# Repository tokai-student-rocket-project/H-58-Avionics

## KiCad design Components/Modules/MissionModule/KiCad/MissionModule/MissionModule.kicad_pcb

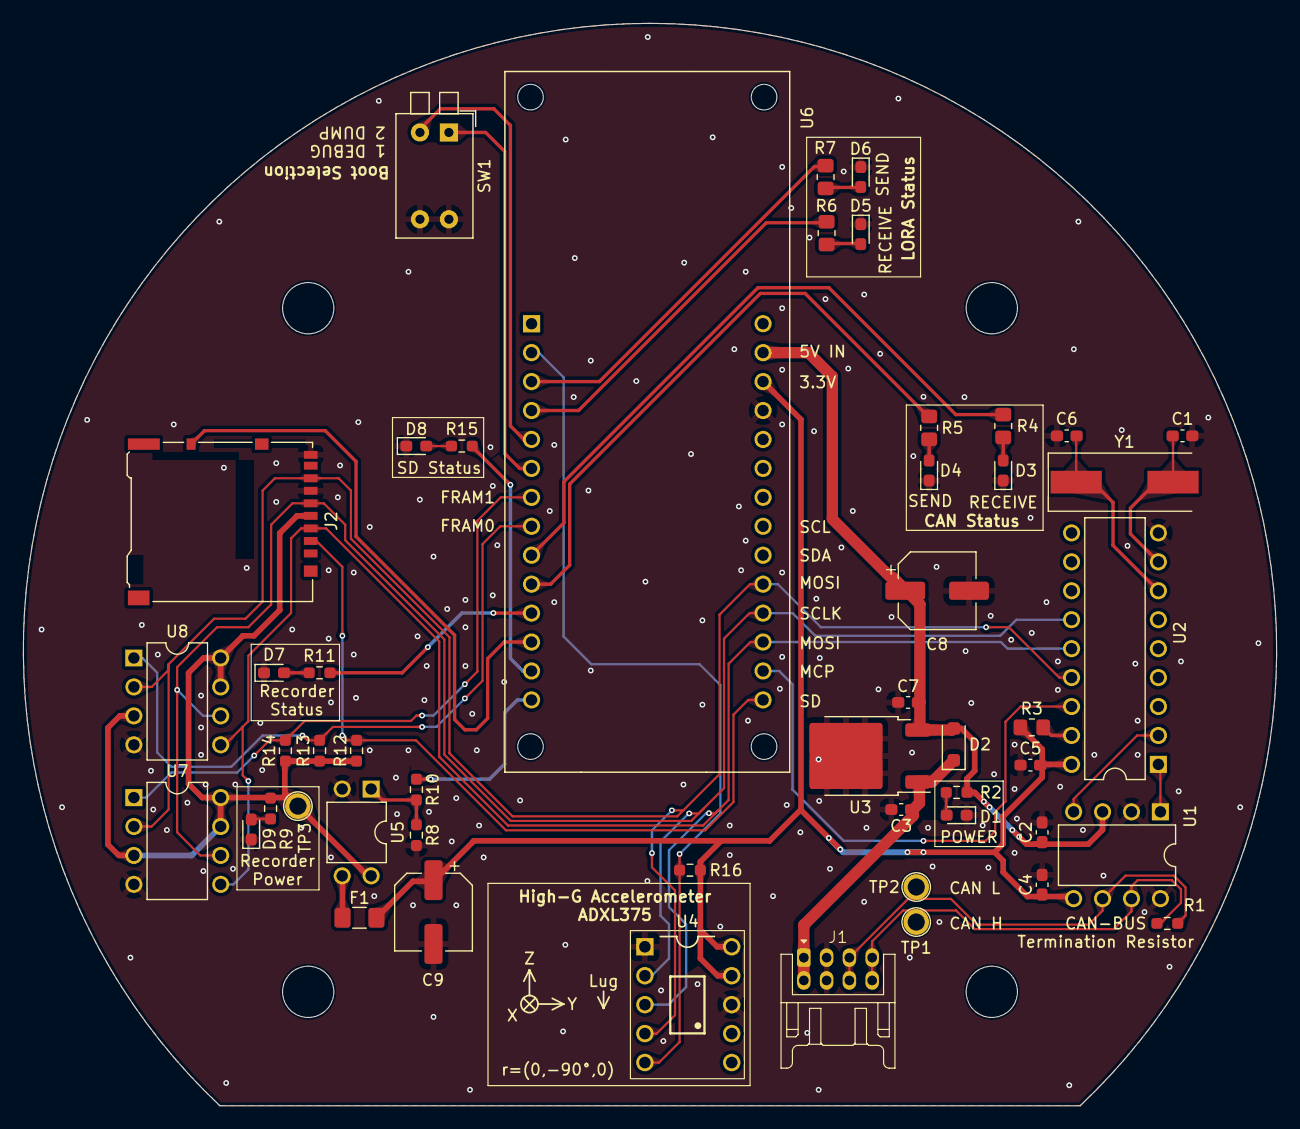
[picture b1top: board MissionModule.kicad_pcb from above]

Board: 2 copper layers, 110.0 x 95.0 mm, 50 parts (0 on the bottom side), 40 nets.

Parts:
C1, C6: 15pF; C_0603_1608Metric_Pad1.08x0.95mm_HandSolder
C2, C4, C5, C7: 0.1uF; C_0603_1608Metric_Pad1.08x0.95mm_HandSolder
C3: 10uF; C_0603_1608Metric_Pad1.08x0.95mm_HandSolder
C8, C9: 47uF; CP_Elec_6.3x5.9
D1, D9: RED; LED_0603_1608Metric_Pad1.05x0.95mm_HandSolder
D2: 1N4007; D_SOD-123F
D3, D4, D5, D6: BLUE; LED_0603_1608Metric_Pad1.05x0.95mm_HandSolder
D7, D8: GREEN; LED_0603_1608Metric_Pad1.05x0.95mm_HandSolder
F1: Polyfuse; Fuse_1206_3216Metric_Pad1.42x1.75mm_HandSolder
J1: Conn_01x08; Hirose_DF11B-8DP-2DS
J2: Micro_SD_Card_Det_Hirose_DM3AT; microSD_HC_Hirose_DM3AT-SF-PEJM5
R1, R8, R10: 120R; R_0603_1608Metric_Pad0.98x0.95mm_HandSolder
R2: 620R; R_0603_1608Metric_Pad0.98x0.95mm_HandSolder
R3: 10kR; R_0805_2012Metric_Pad1.20x1.40mm_HandSolder
R4, R5, R6, R7: 100R; R_0805_2012Metric_Pad1.20x1.40mm_HandSolder
R9, R11, R15: 300R; R_0603_1608Metric_Pad0.98x0.95mm_HandSolder
R12, R13, R14, R16: 4.7kR; R_0603_1608Metric_Pad0.98x0.95mm_HandSolder
SW1: SW_DIP_x02; SW_DIP_SPSTx02_Piano_10.8x6.64mm_W7.62mm_P2.54mm
TP1, TP2, TP3: TestPoint; Pin_D1.0mm_L10.0mm
U1: MCP2562-E-P; DIP-8_W7.62mm
U2: MCP2515-I/P; DIP-18_W7.62mm
U3: NJM7805SDL1; TO-252-2
U4: ADXL375
U5: TLP241B; DIP-4_W7.62mm
U6: ABX00012; ARDUINO_ABX00012
U7, U8: MB85RS2MT; DIP-8_W7.62mm
Y1: 8MHz; Crystal_SMD_HC49-SD

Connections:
+3.3V: C4.1, C5.1, C9.1, F1.1, R3.1, R16.1, U1.5 (Vio), U2.18 (VDD), U4.9 (VS), U4.10 (VDDI/O), U6.26 (+3V3)
+5V: C2.1, C7.1, C8.1, D2.2 (A), R2.1, U1.3 (VDD), U3.3 (OUT), U6.27 (VIN)
+12V: C3.1, D2.1 (K), J1.1, J1.2, U3.1 (IN)
CAN_H: J1.7, J1.8, R1.1, TP1.1, U1.7 (CANH)
CAN_L: J1.5, J1.6, R1.2, TP2.1, U1.6 (CANL)
CAN_RECEIVE_STATUS: R4.1, U6.9 (PA22_TC4-W0/0)
CAN_RX: U1.4 (RXD), U2.2 (RXCAN)
CAN_SEND_STATUS: R5.1, U6.10 (PA23_TC4-W1/1)
CAN_TX: U1.1 (TXD), U2.1 (TXCAN)
DEBUG_MODE: SW1.1, U6.6 (PA05_AIN5/A4)
DUMP_MODE: SW1.2, U6.5 (PA04_AIN4/A3)
GND: C1.1, C2.2, C3.2, C4.2, C5.2, C6.1, C7.2, C8.2, C9.2, D1.1 (K), D3.1 (K), D4.1 (K), D5.1 (K), D6.1 (K), D7.1 (K), D8.1 (K), D9.1 (K), J1.3, J1.4, J2.6 (VSS), J2.9 (DET_B), R8.2, SW1.3, SW1.4, U1.2 (VSS), U1.8 (STBY), U2.9 (VSS), U3.2 (GND), U4.1 (GND), U4.8 (GND), U5.2, U6.25 (GND), U7.4 (GND), U8.4 (GND)
LORA_RECEIVE_STATUS: R6.1, U6.4 (PB03_AIN11/A2)
LORA_SEND_STATUS: R7.1, U6.3 (PB02_AIN10/A1)
MEMORY_POWER: J2.4 (VDD), R9.1, R12.1, R13.1, R14.1, TP3.1, U5.4, U7.3 (~WP), U7.7 (~HOLD), U7.8 (VDD), U8.3 (~WP), U8.7 (~HOLD), U8.8 (VDD)
MEMORY_POWER_CONTROL: R10.1, U6.14 (PB11_TCC0-W5/~5)
unnamed: D1.2 (A), R2.2
unnamed: D3.2 (A), R4.2
unnamed: D4.2 (A), R5.2
unnamed: D5.2 (A), R6.2
unnamed: D6.2 (A), R7.2
unnamed: D7.2 (A), R11.2
unnamed: D8.2 (A), R15.2
unnamed: D9.2 (A), R9.2
unnamed: F1.2, U5.3
unnamed: R8.1, R10.2, U5.1
unnamed: R3.2, U2.17 (~RESET)
OSC1: C1.2, U2.8 (OSC1), Y1.2
OSC2: C6.2, U2.7 (OSC2), Y1.1
RECORD_STATUS: R11.1, U6.11 (PA10_TCC0-W2/~2)
SD_CHECK: J2.10 (DET_A), U6.12 (PA11_TCC0-W3/~3)
SD_STATUS: R15.1, U6.13 (PB10_TCC0-W4/~4)
SPI_CS_ADXL: R16.2, U4.5 (~CS), U6.2 (PA02_AIN0/DAC0/A0)
SPI_CS_FRAM0: R13.2, U6.8 (PA07_AIN7/A6), U8.1 (~CS)
SPI_CS_FRAM1: R14.2, U6.7 (PA06_AIN6/A5), U7.1 (~CS)
SPI_CS_MCP: U2.16 (~CS), U6.16 (PA21_TCC0-W7)
SPI_CS_SD: J2.2 (DAT3/CD), R12.2, U6.15 (PA20_TCC0-W6)
SPI_MISO: J2.7 (DAT0), U2.15 (SO), U4.4 (SDO/ALT_ADDRESS), U6.19 (PA19_S1_MISO), U7.2 (SO), U8.2 (SO)
SPI_MOSI: J2.3 (CMD), U2.14 (SI), U4.3 (SDA/SDI/SDIO), U6.17 (PA16_S1_MOSI), U7.5 (SI), U8.5 (SI)
SPI_SCLK: J2.5 (CLK), U2.13 (SCK), U4.2 (SCK/SCLK), U6.18 (PA17_S1_SCK), U7.6 (SCK), U8.6 (SCK)

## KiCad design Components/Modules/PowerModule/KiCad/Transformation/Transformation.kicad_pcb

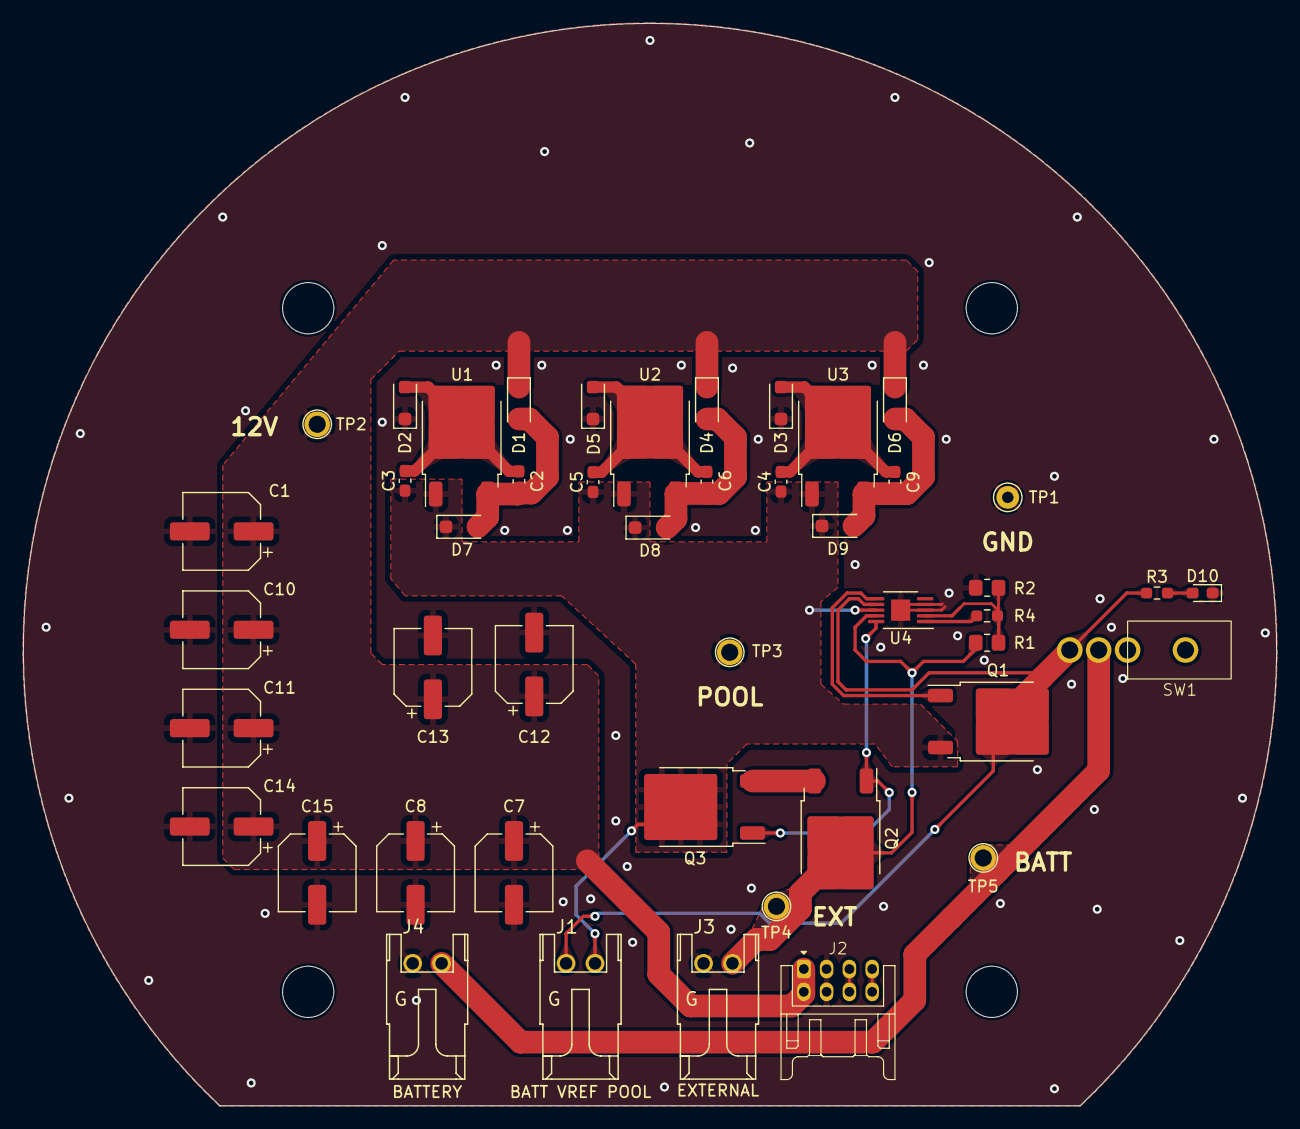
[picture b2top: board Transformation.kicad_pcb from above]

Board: 2 copper layers, 110.0 x 95.0 mm, 46 parts (0 on the bottom side), 20 nets.

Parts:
C1, C7, C8, C10, C11, C12, C13, C14, C15: 100μF; CP_Elec_6.3x5.9
C2, C6, C9: 0.1μF; C_0603_1608Metric_Pad1.08x0.95mm_HandSolder
C3, C4, C5: 10μF; C_0603_1608Metric_Pad1.08x0.95mm_HandSolder
D1, D2, D3, D4, D5, D6, D7, D8, D9: 1N4007; D_SOD-123F
D10: RED; LED_0603_1608Metric_Pad1.05x0.95mm_HandSolder
J1, J3, J4: Conn_01x02_Pin; Hirose_DF1B
J2: Conn_01x08; Hirose_DF11B-8DP-2DS
Q1, Q2, Q3: TJ8S06M3L; TO-252-2
R1: 120kΩ; R_0805_2012Metric_Pad1.20x1.40mm_HandSolder
R2: 10kΩ; R_0805_2012Metric_Pad1.20x1.40mm_HandSolder
R3: 2kΩ; R_0603_1608Metric_Pad0.98x0.95mm_HandSolder
R4: 68kΩ; R_0603_1608Metric_Pad0.98x0.95mm_HandSolder
SW1: SW_SPDT; 2MS1T1B4M7QES
TP1, TP2, TP3, TP4, TP5: TestPoint; Pin_D1.0mm_L10.0mm
U1, U2, U3: NJM7812SDL1; TO-252-2
U4: LTC4416EMS#PBF; MSOP-10-1EP_3x3mm_P0.5mm_EP1.68x1.88mm

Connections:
+12V: C1.1, C7.1, C8.1, C10.1, C11.1, C12.1, C13.1, C14.1, C15.1, D1.1 (K), D4.1 (K), D6.1 (K), J2.1, J2.2, TP2.1
+BATT: J1.1, Q1.2 (D), R3.1, SW1.3 (C), U4.7 (V2)
+VDC: J3.2, Q2.2 (D), R1.2, TP4.1, U4.9 (V1)
+VSW: C3.1, C4.1, C5.1, D7.1 (K), D8.1 (K), D9.1 (K), J1.2, Q1.3 (S), Q3.2 (D), TP3.1, U1.1 (IN), U2.1 (IN), U3.1 (IN), U4.8 (VS)
GND: C1.2, C7.2, C8.2, C10.2, C11.2, C12.2, C13.2, C14.2, C15.2, D2.1 (K), D3.1 (K), D5.1 (K), D10.1 (K), J2.3, J2.4, J3.1, J4.1, R2.1, TP1.1, U4.3 (GND), U4.4 (*E2), U4.11
unnamed: C2.1, D1.2 (A), D7.2 (A), U1.3 (OUT)
unnamed: C2.2, C3.2, D2.2 (A), U1.2 (GND)
unnamed: C4.2, C9.2, D3.2 (A), U3.2 (GND)
unnamed: C6.1, D4.2 (A), D8.2 (A), U2.3 (OUT)
unnamed: C5.2, C6.2, D5.2 (A), U2.2 (GND)
unnamed: C9.1, D6.2 (A), D9.2 (A), U3.3 (OUT)
unnamed: D10.2 (A), R3.2
unnamed: J2.5, J2.6
unnamed: J2.7, J2.8
unnamed: J4.2, SW1.2 (B), TP5.1
unnamed: Q1.1 (G), U4.6 (G2)
unnamed: Q2.1 (G), Q3.1 (G), U4.10 (G1)
unnamed: Q2.3 (S), Q3.3 (S)
unnamed: R1.1, R2.2, R4.1, U4.2 (E1)
unnamed: R4.2, U4.1 (H1)

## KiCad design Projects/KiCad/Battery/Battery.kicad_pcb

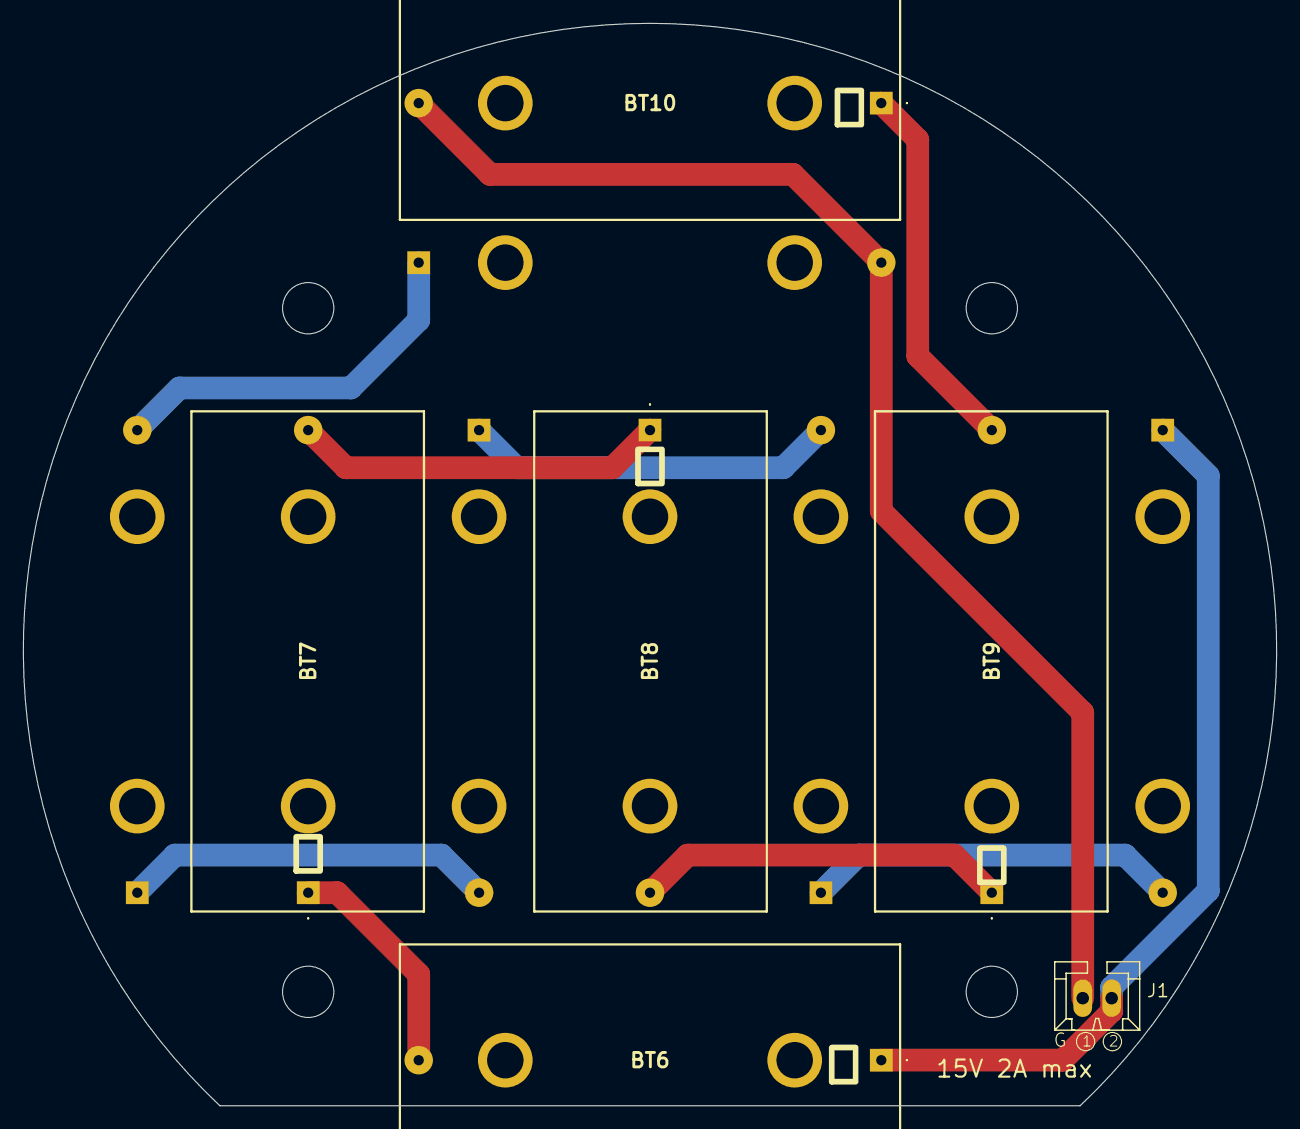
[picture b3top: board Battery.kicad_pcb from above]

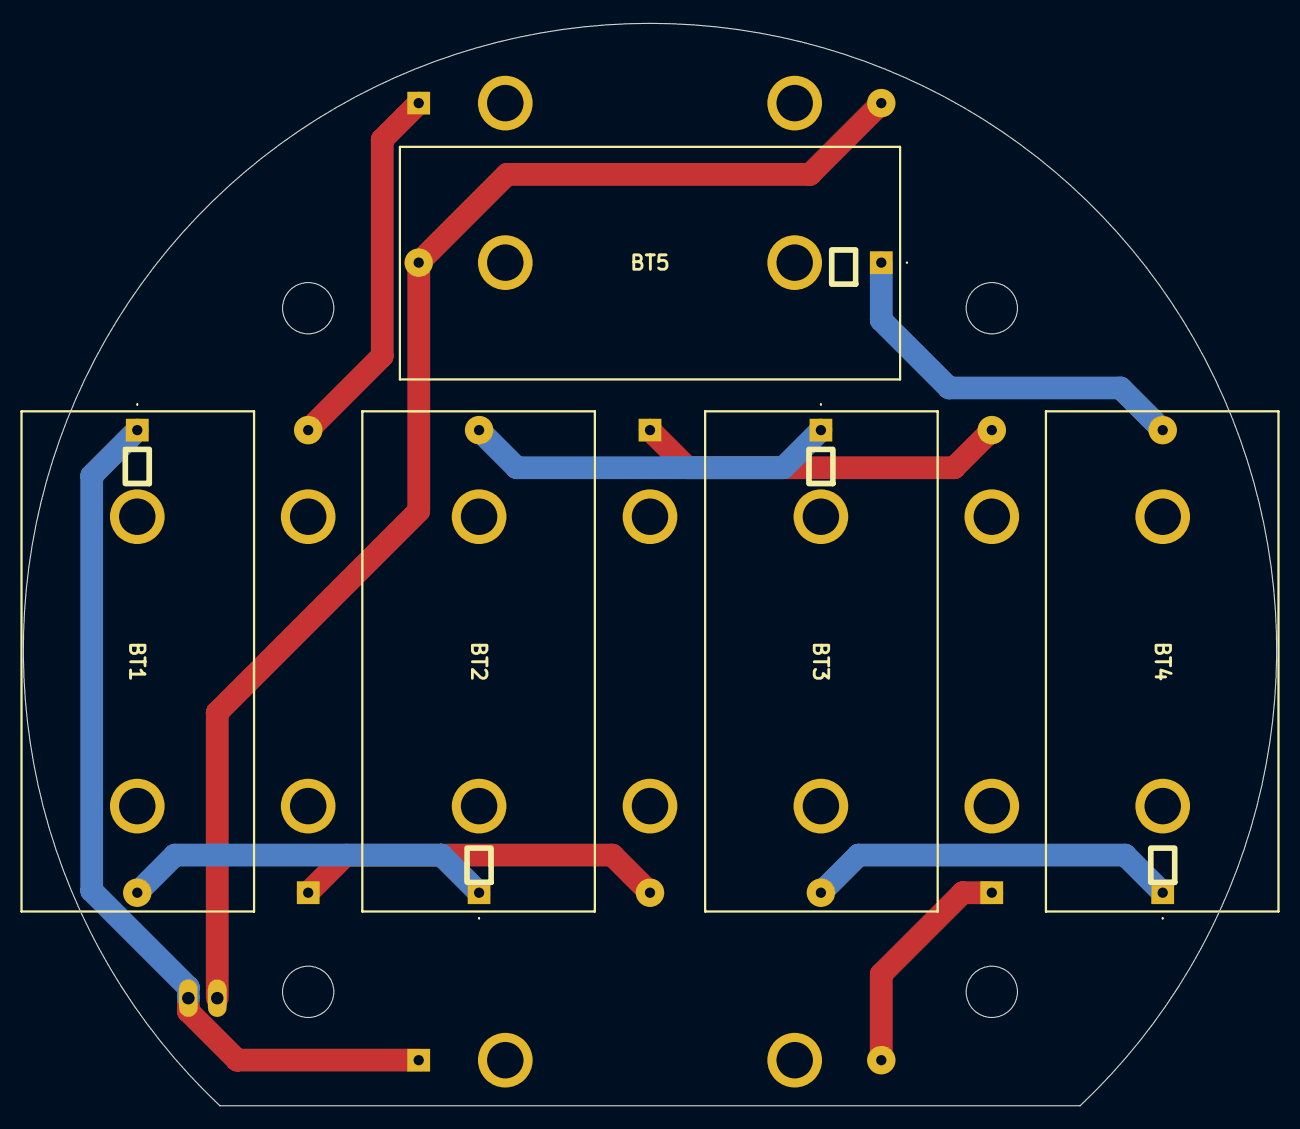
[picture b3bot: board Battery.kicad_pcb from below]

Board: 2 copper layers, 110.0 x 95.0 mm, 11 parts (5 on the bottom side), 10 nets.

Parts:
BT1, BT2, BT3, BT4, BT5, BT6, BT7, BT8, BT9, BT10: Battery_Cell; CR123APC
J1: Conn_01x02_Socket; CONNECTOR_2-STRAIGHT

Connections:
unnamed: BT1.1 (+), BT6.1 (+), J1.2
unnamed: BT1.2 (-), BT2.1 (+)
unnamed: BT2.2 (-), BT3.1 (+)
unnamed: BT3.2 (-), BT4.1 (+)
unnamed: BT4.2 (-), BT5.1 (+)
unnamed: BT6.2 (-), BT7.1 (+)
unnamed: BT7.2 (-), BT8.1 (+)
unnamed: BT8.2 (-), BT9.1 (+)
unnamed: BT9.2 (-), BT10.1 (+)
unnamed: BT5.2 (-), BT10.2 (-), J1.1

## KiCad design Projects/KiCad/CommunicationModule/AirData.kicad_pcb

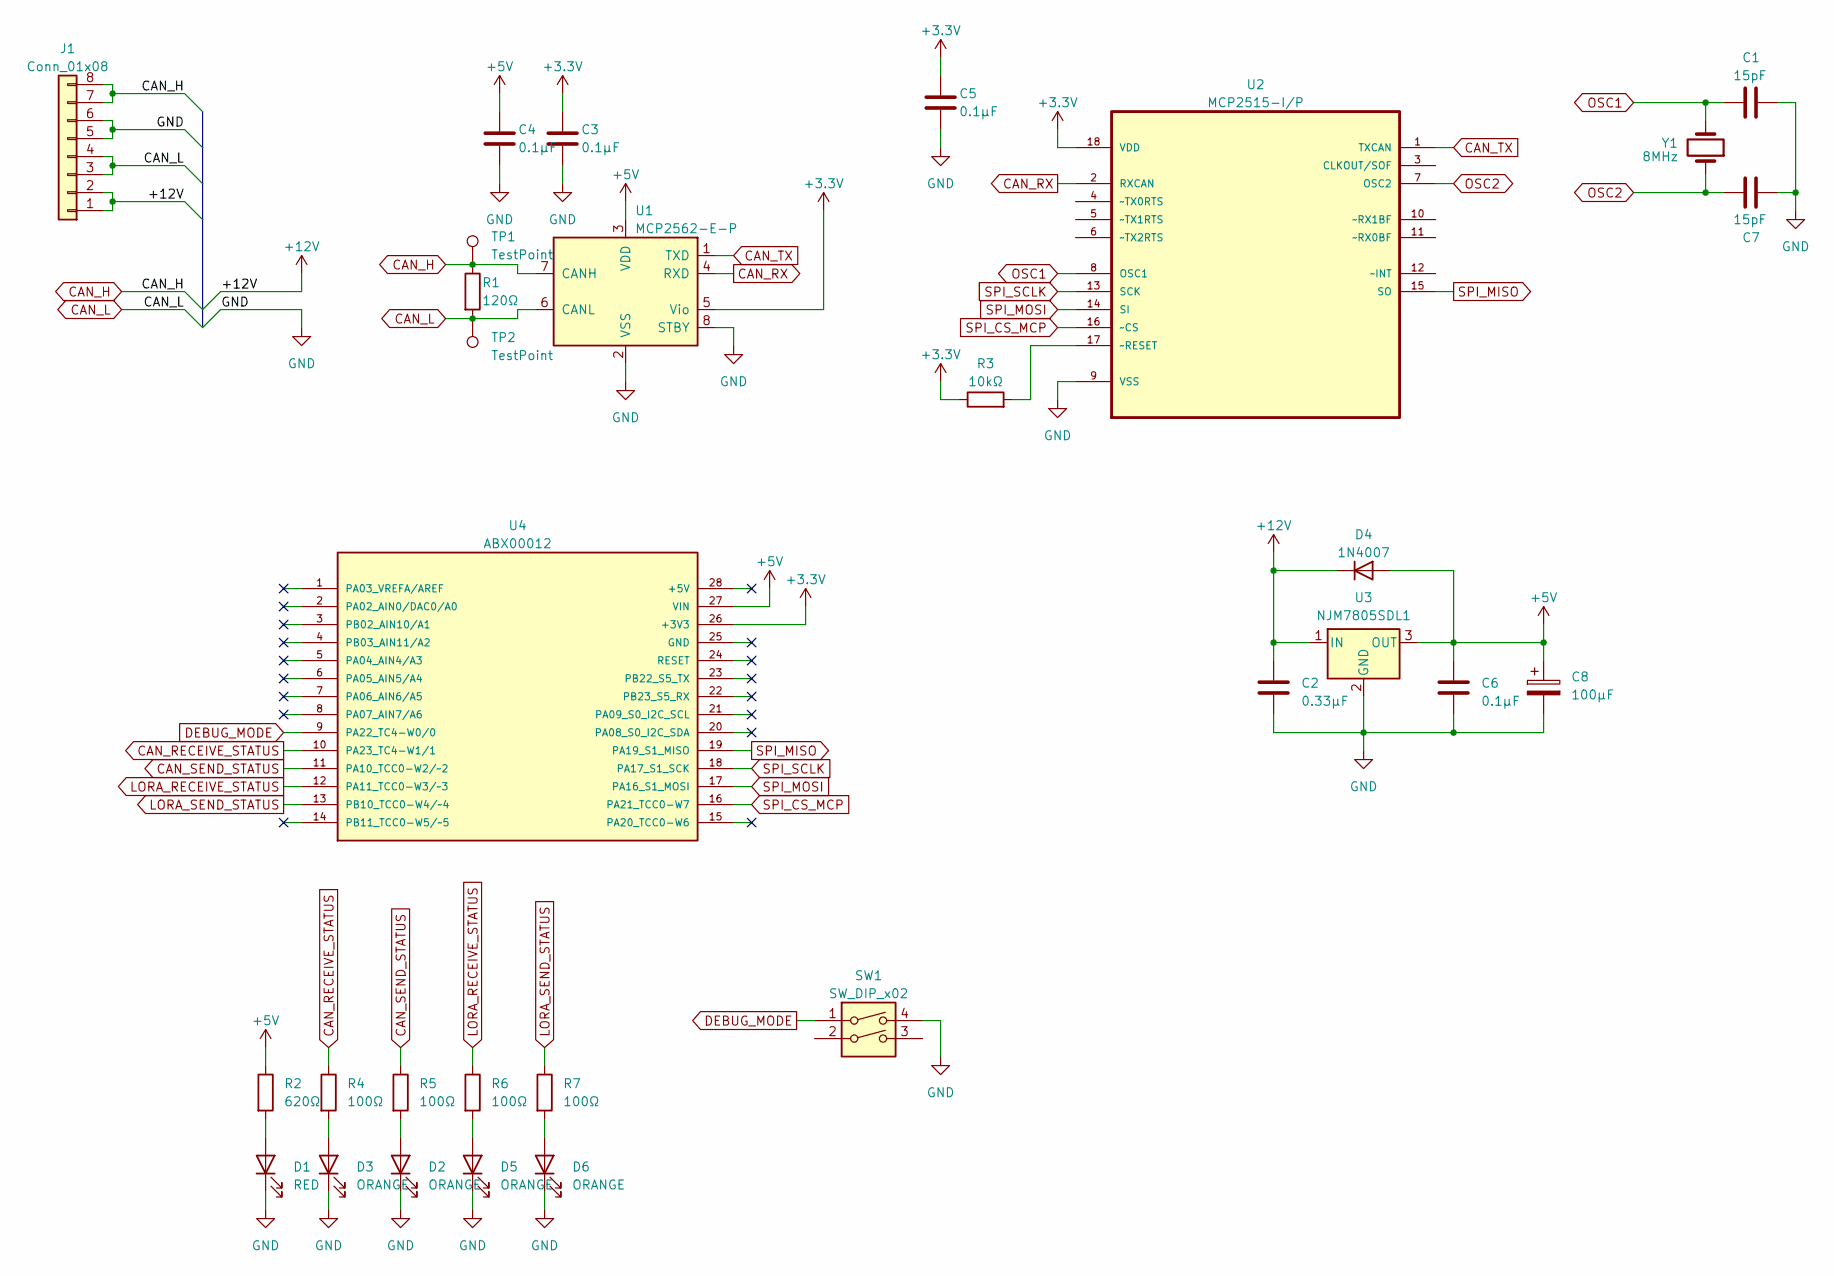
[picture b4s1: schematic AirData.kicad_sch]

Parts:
C1, C7: 15pF; C_0603_1608Metric_Pad1.08x0.95mm_HandSolder
C2: 0.33μF; C_0805_2012Metric_Pad1.18x1.45mm_HandSolder
C3, C4, C5, C6: 0.1μF; C_0805_2012Metric_Pad1.18x1.45mm_HandSolder
C8: 100μF; CP_Elec_6.3x7.7
D1: RED; LED_0603_1608Metric_Pad1.05x0.95mm_HandSolder
D2, D3, D5, D6: ORANGE; LED_0603_1608Metric_Pad1.05x0.95mm_HandSolder
D4: 1N4007; D_SOD-123F
J1: Conn_01x08; Hirose_DF11-8DP-2DSA_2x04_P2.00mm_Vertical
R1: 120Ω; R_0603_1608Metric_Pad0.98x0.95mm_HandSolder
R2: 620Ω; R_0603_1608Metric_Pad0.98x0.95mm_HandSolder
R3: 10kΩ; R_0603_1608Metric_Pad0.98x0.95mm_HandSolder
R4, R5, R6, R7: 100Ω; R_0603_1608Metric_Pad0.98x0.95mm_HandSolder
SW1: SW_DIP_x02; SW_DIP_SPSTx02_Piano_10.8x6.64mm_W7.62mm_P2.54mm
TP1, TP2: TestPoint; Pin_D1.0mm_L10.0mm
U1: MCP2562-E-P; DIP-8_W7.62mm
U2: MCP2515-I/P; DIP-18_W7.62mm; MPN MCP2515-I/P
U3: NJM7805SDL1; TO-252-3_TabPin2
U4: ABX00012; ARDUINO_ABX00012; PARTREV 5
Y1: 8MHz; Crystal_HC49-U_Vertical

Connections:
+3.3V: C3.1, C5.1, R3.1, U1.5 (Vio), U2.18 (VDD), U4.26 (+3V3)
+5V: C4.1, C6.1, C8.1, D4.2 (A), R2.1, U1.3 (VDD), U3.3 (OUT), U4.27 (VIN)
+12V: C2.1, D4.1 (K), J1.1, J1.2, U3.1 (IN)
CAN_H: J1.7, J1.8, R1.1, TP1.1, U1.7 (CANH)
CAN_L: J1.3, J1.4, R1.2, TP2.1, U1.6 (CANL)
CAN_RECEIVE_STATUS: R4.1, U4.10 (PA23_TC4-W1/1)
CAN_RX: U1.4 (RXD), U2.2 (RXCAN)
CAN_SEND_STATUS: R5.1, U4.11 (PA10_TCC0-W2/~2)
CAN_TX: U1.1 (TXD), U2.1 (TXCAN)
DEBUG_MODE: SW1.1, U4.9 (PA22_TC4-W0/0)
GND: C1.1, C2.2, C3.2, C4.2, C5.2, C6.2, C7.1, C8.2, D1.1 (K), D2.1 (K), D3.1 (K), D5.1 (K), D6.1 (K), J1.5, J1.6, SW1.4, U1.2 (VSS), U1.8 (STBY), U2.9 (VSS), U3.2 (GND)
LORA_RECEIVE_STATUS: R6.1, U4.12 (PA11_TCC0-W3/~3)
LORA_SEND_STATUS: R7.1, U4.13 (PB10_TCC0-W4/~4)
unnamed: D1.2 (A), R2.2
unnamed: D2.2 (A), R5.2
unnamed: D3.2 (A), R4.2
unnamed: D5.2 (A), R6.2
unnamed: D6.2 (A), R7.2
unnamed: R3.2, U2.17 (~RESET)
OSC1: C1.2, U2.8 (OSC1), Y1.2
OSC2: C7.2, U2.7 (OSC2), Y1.1
SPI_CS_MCP: U2.16 (~CS), U4.16 (PA21_TCC0-W7)
SPI_MISO: U2.15 (SO), U4.19 (PA19_S1_MISO)
SPI_MOSI: U2.14 (SI), U4.17 (PA16_S1_MOSI)
SPI_SCLK: U2.13 (SCK), U4.18 (PA17_S1_SCK)

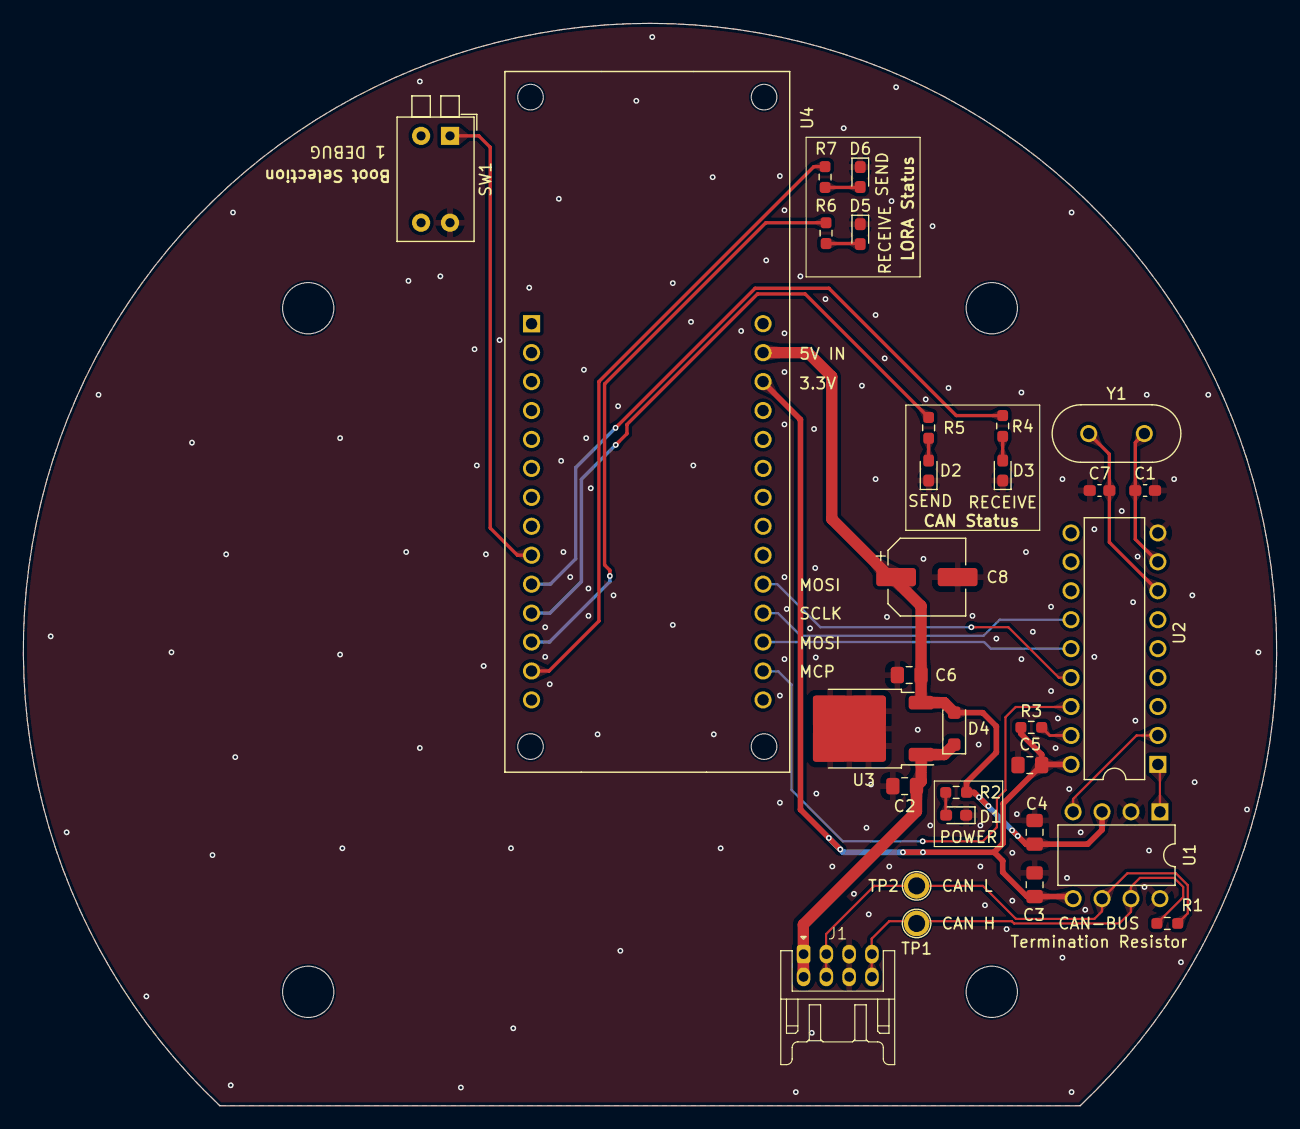
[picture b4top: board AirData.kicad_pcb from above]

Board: 2 copper layers, 110.0 x 95.0 mm, 30 parts (0 on the bottom side), 25 nets.

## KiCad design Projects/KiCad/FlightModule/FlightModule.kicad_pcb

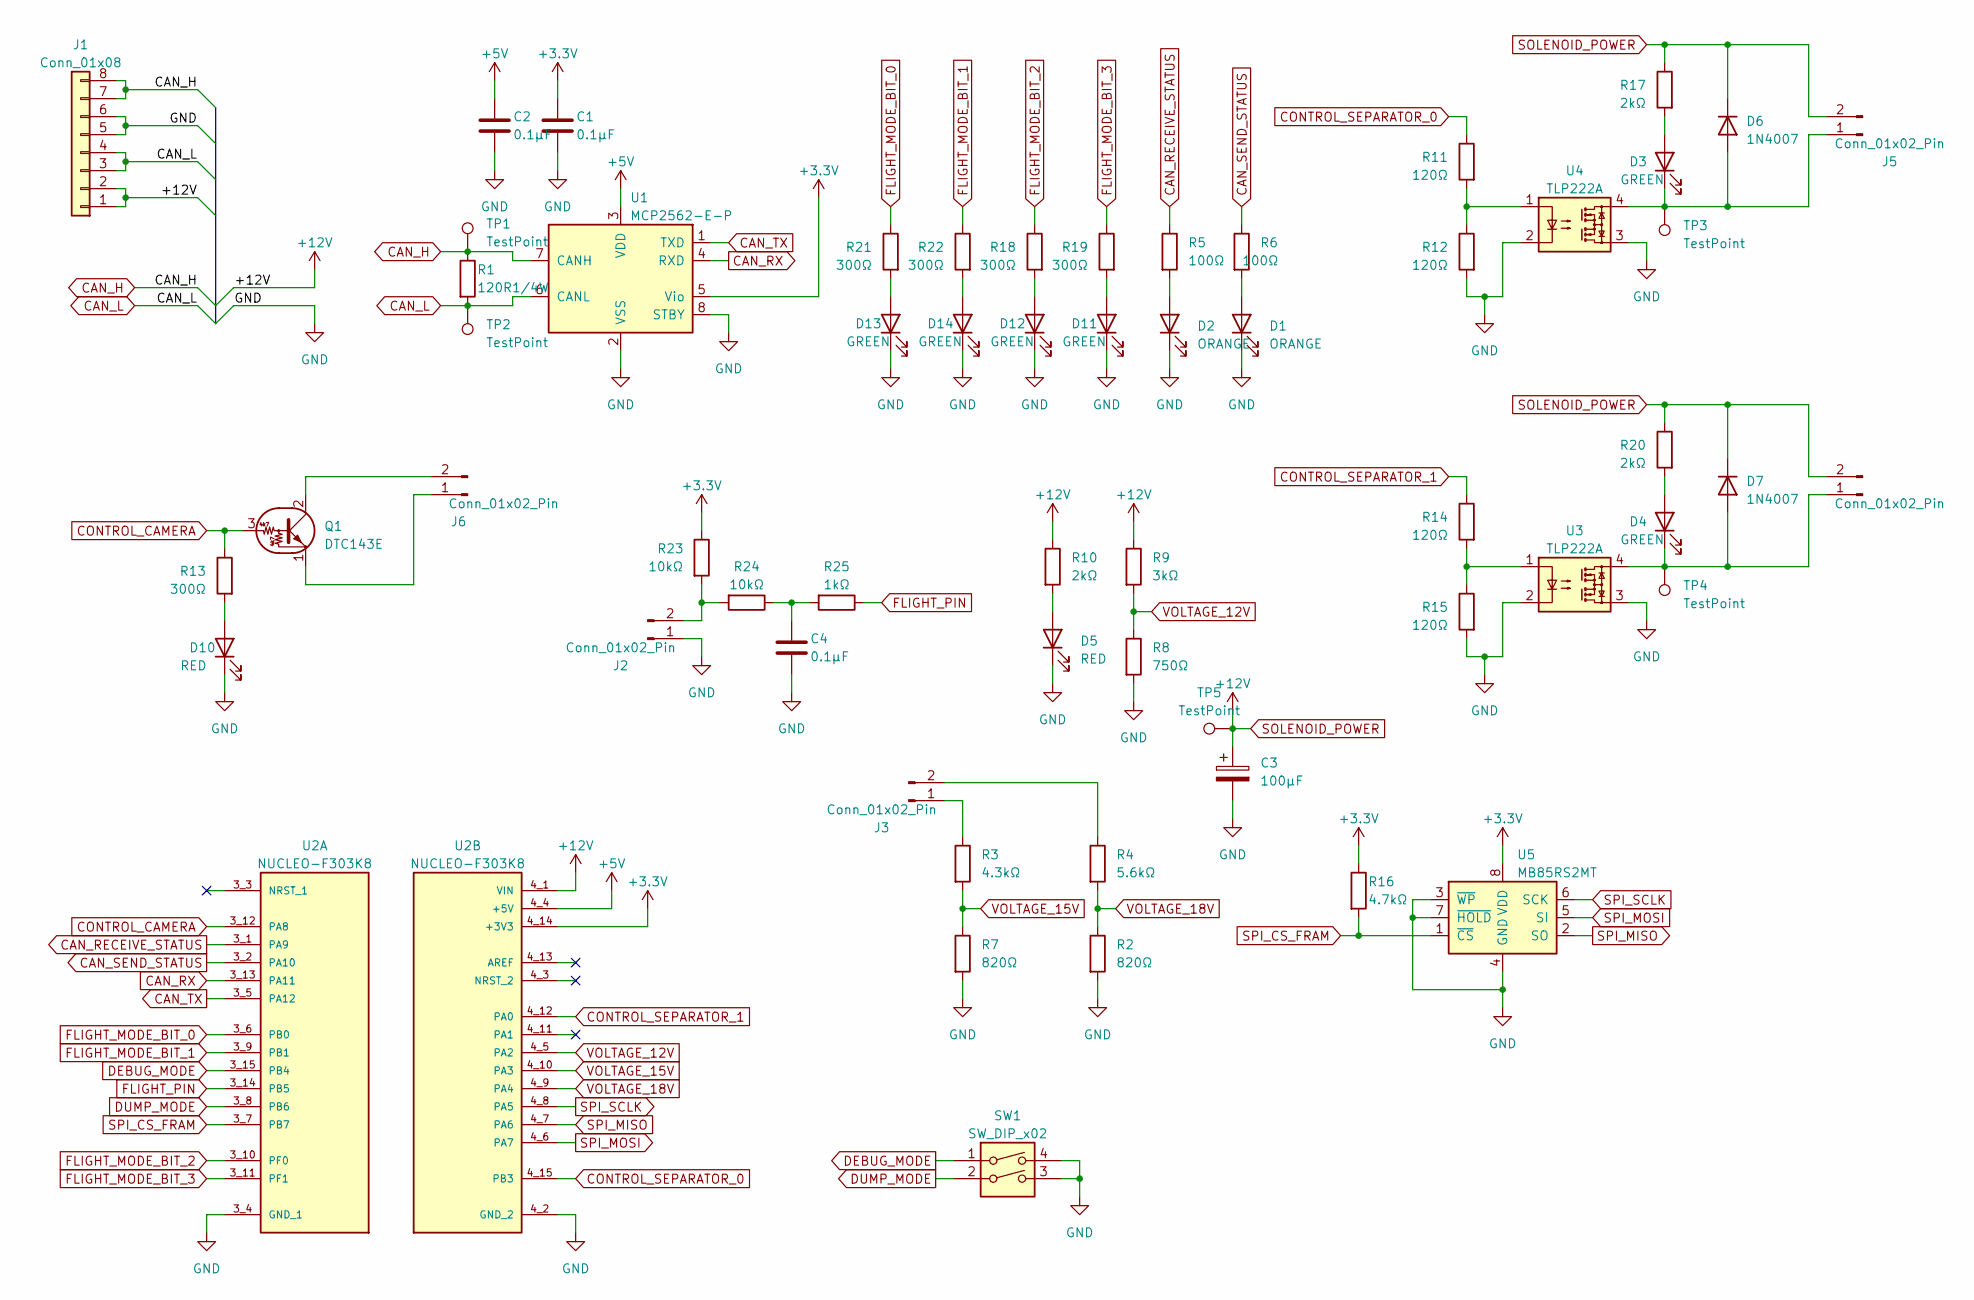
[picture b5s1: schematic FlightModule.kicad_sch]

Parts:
C1, C2, C4: 0.1μF; C_0805_2012Metric_Pad1.18x1.45mm_HandSolder
C3: 100μF; CP_Elec_6.3x7.7
D1, D2: ORANGE; LED_0603_1608Metric_Pad1.05x0.95mm_HandSolder
D3, D4, D11, D12, D13, D14: GREEN; LED_0603_1608Metric_Pad1.05x0.95mm_HandSolder
D5, D10: RED; LED_0603_1608Metric_Pad1.05x0.95mm_HandSolder
D6, D7: 1N4007; D_SOD-123F
J1: Conn_01x08; Hirose_DF11-8DP-2DSA_2x04_P2.00mm_Vertical
J2, J3, J4, J5, J6: Conn_01x02_Pin; Hirose_DF1B
Q1: DTC143E; TO-92_Inline
R1: 120R1/4W; R_0603_1608Metric_Pad0.98x0.95mm_HandSolder
R2, R7: 820Ω; R_0603_1608Metric_Pad0.98x0.95mm_HandSolder
R3: 4.3kΩ; R_0603_1608Metric_Pad0.98x0.95mm_HandSolder
R4: 5.6kΩ; R_0603_1608Metric_Pad0.98x0.95mm_HandSolder
R5, R6: 100Ω; R_0603_1608Metric_Pad0.98x0.95mm_HandSolder
R8: 750Ω; R_0603_1608Metric_Pad0.98x0.95mm_HandSolder
R9: 3kΩ; R_0603_1608Metric_Pad0.98x0.95mm_HandSolder
R10, R17, R20: 2kΩ; R_0603_1608Metric_Pad0.98x0.95mm_HandSolder
R11, R12, R14, R15: 120Ω; R_0603_1608Metric_Pad0.98x0.95mm_HandSolder
R13, R18, R19, R21, R22: 300Ω; R_0603_1608Metric_Pad0.98x0.95mm_HandSolder
R16: 4.7kΩ; R_0603_1608Metric_Pad0.98x0.95mm_HandSolder
R23, R24: 10kΩ; R_0603_1608Metric_Pad0.98x0.95mm_HandSolder
R25: 1kΩ; R_0603_1608Metric_Pad0.98x0.95mm_HandSolder
SW1: SW_DIP_x02; SW_DIP_SPSTx02_Piano_10.8x6.64mm_W7.62mm_P2.54mm
TP1, TP2, TP3, TP4, TP5: TestPoint; Pin_D1.0mm_L10.0mm
U1: MCP2562-E-P; DIP-8_W7.62mm
U2: NUCLEO-F303K8; MODULE_NUCLEO-F303K8; PARTREV 5
U3, U4: TLP222A; DIP-4_W7.62mm
U5: MB85RS2MT; DIP-8_W7.62mm

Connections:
+3.3V: C1.1, R16.1, R23.1, U1.5 (Vio), U2.4_14 (+3V3), U5.8 (VDD)
+5V: C2.1, U1.3 (VDD), U2.4_4 (+5V)
CAN_H: J1.7, J1.8, R1.1, TP1.1, U1.7 (CANH)
CAN_L: J1.3, J1.4, R1.2, TP2.1, U1.6 (CANL)
CAN_RECEIVE_STATUS: R5.1, U2.3_1 (PA9)
CAN_RX: U1.4 (RXD), U2.3_13 (PA11)
CAN_SEND_STATUS: R6.1, U2.3_2 (PA10)
CAN_TX: U1.1 (TXD), U2.3_5 (PA12)
CONTROL_CAMERA: Q1.3 (B), R13.1, U2.3_12 (PA8)
CONTROL_SEPARATOR_0: R11.1, U2.4_15 (PB3)
CONTROL_SEPARATOR_1: R14.1, U2.4_12 (PA0)
DEBUG_MODE: SW1.1, U2.3_15 (PB4)
DUMP_MODE: SW1.2, U2.3_8 (PB6)
FLIGHT_MODE_BIT_0: R21.1, U2.3_6 (PB0)
FLIGHT_MODE_BIT_1: R22.1, U2.3_9 (PB1)
FLIGHT_MODE_BIT_2: R18.1, U2.3_10 (PF0)
FLIGHT_MODE_BIT_3: R19.1, U2.3_11 (PF1)
FLIGHT_PIN: R25.1, U2.3_14 (PB5)
GND: C1.2, C2.2, C3.2, C4.2, D1.1 (K), D2.1 (K), D5.1 (K), D10.1 (K), D11.1 (K), D12.1 (K), D13.1 (K), D14.1 (K), J1.5, J1.6, J2.1, R2.2, R7.2, R8.2, R12.2, R15.2, SW1.3, SW1.4, U1.2 (VSS), U1.8 (STBY), U2.3_4 (GND_1), U2.4_2 (GND_2), U3.2, U3.3, U4.2, U4.3, U5.3 (~WP), U5.4 (GND), U5.7 (~HOLD)
unnamed: C4.1, R24.1, R25.2
unnamed: D1.2 (A), R6.2
unnamed: D2.2 (A), R5.2
unnamed: D3.2 (A), R17.2
unnamed: D3.1 (K), D6.2 (A), J5.1, TP3.1, U4.4
unnamed: D4.2 (A), R20.2
unnamed: D4.1 (K), D7.2 (A), J4.1, TP4.1, U3.4
unnamed: D5.2 (A), R10.2
unnamed: D10.2 (A), R13.2
unnamed: D11.2 (A), R19.2
unnamed: D12.2 (A), R18.2
unnamed: D13.2 (A), R21.2
unnamed: D14.2 (A), R22.2
unnamed: J2.2, R23.2, R24.2
unnamed: J3.1, R3.1
unnamed: J3.2, R4.1
unnamed: J6.1, Q1.1 (E)
unnamed: J6.2, Q1.2 (C)
unnamed: R11.2, R12.1, U4.1
unnamed: R14.2, R15.1, U3.1
SOLENOID_POWER: C3.1, D6.1 (K), D7.1 (K), J1.1, J1.2, J4.2, J5.2, R9.1, R10.1, R17.1, R20.1, TP5.1, U2.4_1 (VIN)
SPI_CS_FRAM: R16.2, U2.3_7 (PB7), U5.1 (~CS)
SPI_MISO: U2.4_7 (PA6), U5.2 (SO)
SPI_MOSI: U2.4_6 (PA7), U5.5 (SI)
SPI_SCLK: U2.4_8 (PA5), U5.6 (SCK)
VOLTAGE_12V: R8.1, R9.2, U2.4_5 (PA2)
VOLTAGE_BATT: R3.2, R7.1, U2.4_10 (PA3)
VOLTAGE_VSW: R2.1, R4.2, U2.4_9 (PA4)

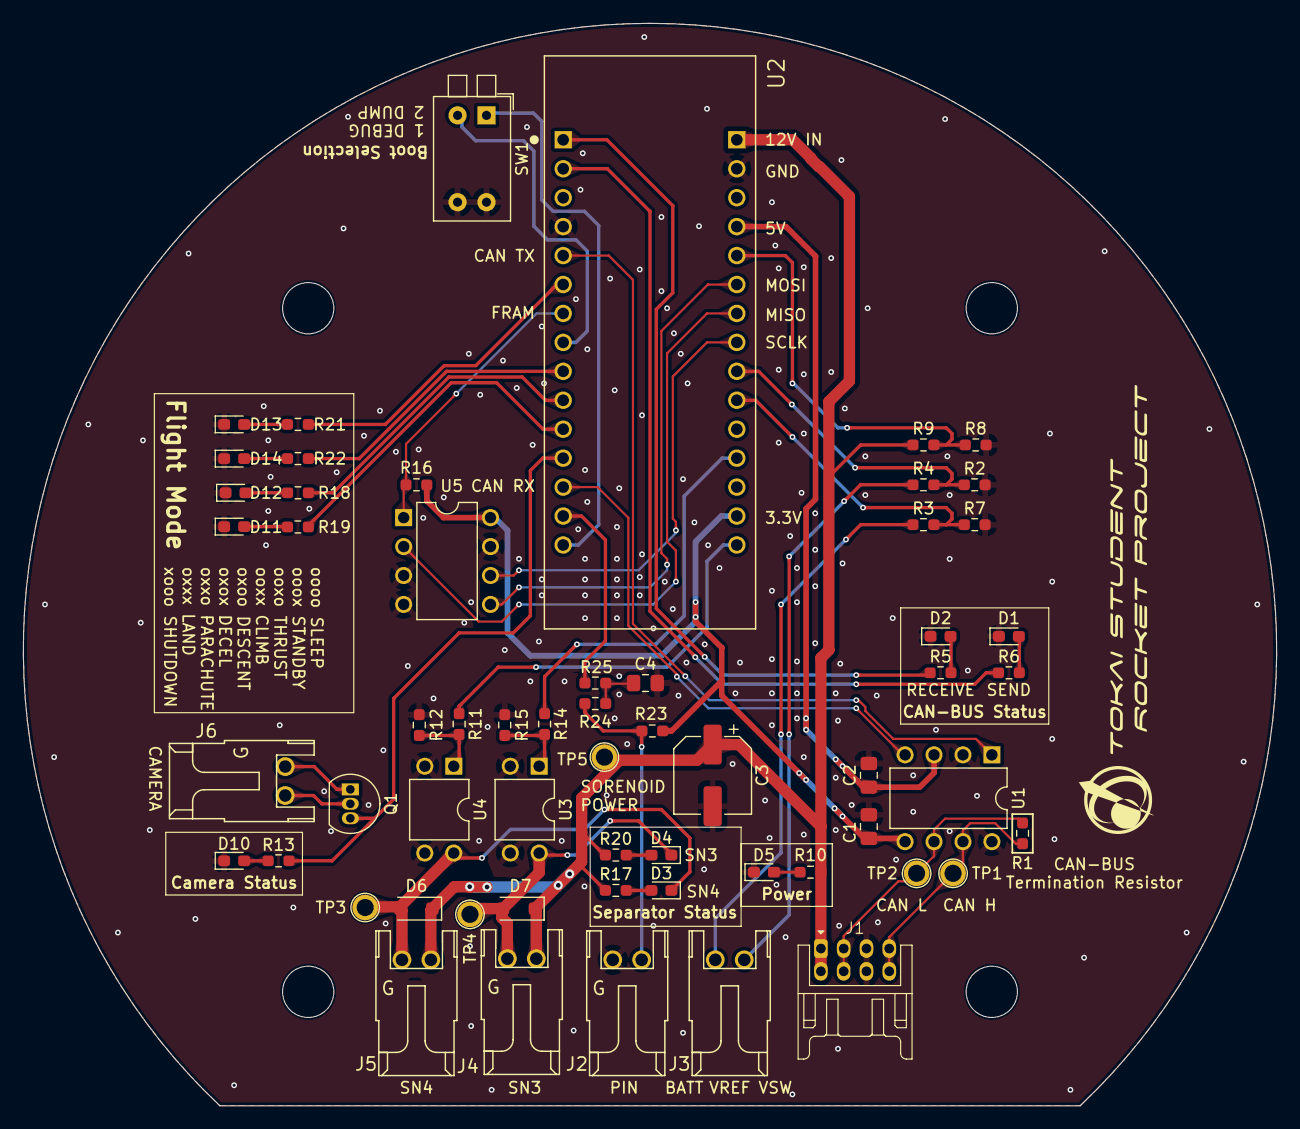
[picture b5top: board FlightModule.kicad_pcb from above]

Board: 2 copper layers, 110.0 x 95.0 mm, 60 parts (0 on the bottom side), 47 nets.

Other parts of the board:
e: MountingHole_4.5mm
